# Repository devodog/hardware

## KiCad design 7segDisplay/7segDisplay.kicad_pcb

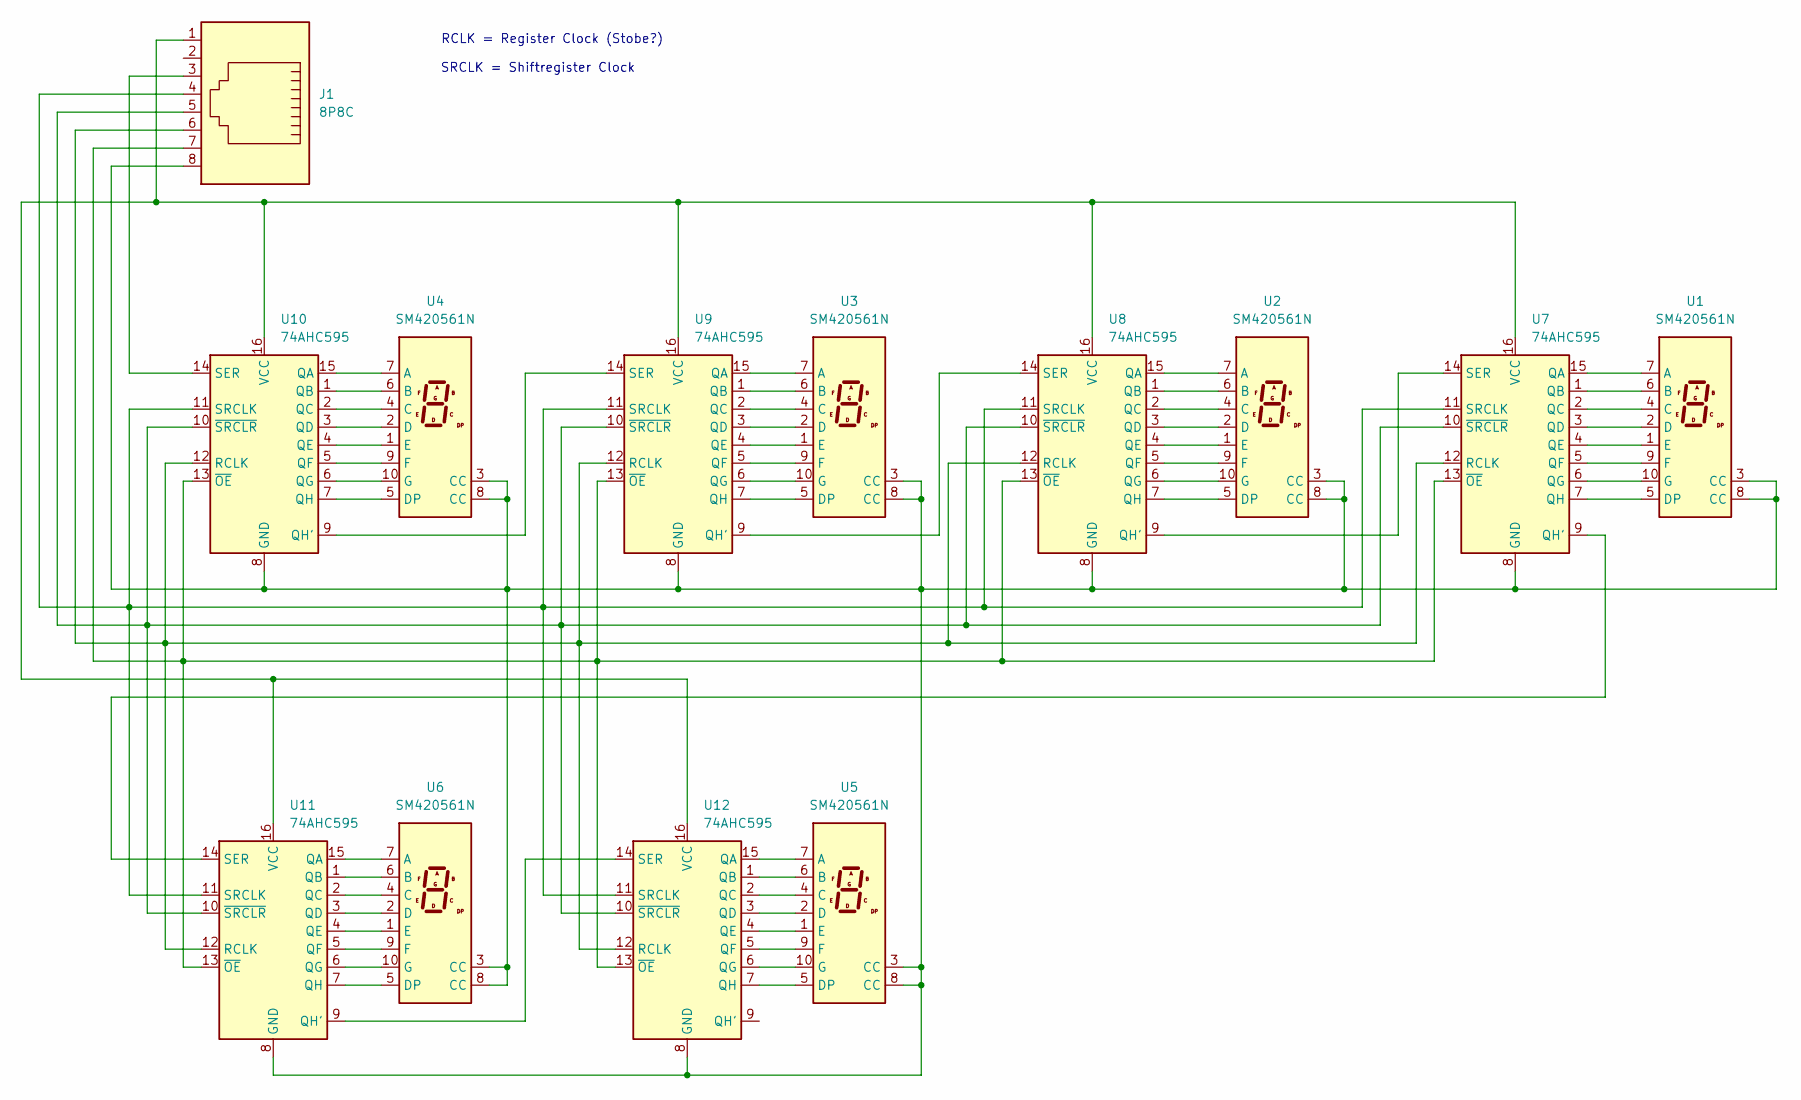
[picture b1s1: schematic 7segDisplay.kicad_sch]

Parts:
J1: 8P8C; RJ45_Amphenol_54602-x08_Horizontal
U1, U2, U3, U4, U5, U6: SM420561N; 7SegmentLED_LTS6760_LTS6780
U7, U8, U9, U10, U11, U12: 74AHC595; DIP-16_W7.62mm_LongPads

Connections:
unnamed: U1.7 (A), U7.15 (QA)
unnamed: U1.6 (B), U7.1 (QB)
unnamed: U1.4 (C), U7.2 (QC)
unnamed: U1.2 (D), U7.3 (QD)
unnamed: U1.5 (DP), U7.7 (QH)
unnamed: U1.1 (E), U7.4 (QE)
unnamed: U1.9 (F), U7.5 (QF)
unnamed: U1.10 (G), U7.6 (QG)
unnamed: U2.7 (A), U8.15 (QA)
unnamed: U2.6 (B), U8.1 (QB)
unnamed: U2.4 (C), U8.2 (QC)
unnamed: U2.2 (D), U8.3 (QD)
unnamed: U2.5 (DP), U8.7 (QH)
unnamed: U2.1 (E), U8.4 (QE)
unnamed: U2.9 (F), U8.5 (QF)
unnamed: U2.10 (G), U8.6 (QG)
unnamed: U3.7 (A), U9.15 (QA)
unnamed: U3.6 (B), U9.1 (QB)
unnamed: U3.4 (C), U9.2 (QC)
unnamed: U3.2 (D), U9.3 (QD)
unnamed: U3.5 (DP), U9.7 (QH)
unnamed: U3.1 (E), U9.4 (QE)
unnamed: U3.9 (F), U9.5 (QF)
unnamed: U3.10 (G), U9.6 (QG)
unnamed: U7.14 (SER), U8.9 (QH')
unnamed: U8.14 (SER), U9.9 (QH')
unnamed: J1.8, U1.3 (CC), U1.8 (CC), U2.3 (CC), U2.8 (CC), U3.3 (CC), U3.8 (CC), U4.3 (CC), U4.8 (CC), U5.3 (CC), U5.8 (CC), U6.3 (CC), U6.8 (CC), U7.8 (GND), U8.8 (GND), U9.8 (GND), U10.8 (GND), U11.8 (GND), U12.8 (GND)
unnamed: U4.7 (A), U10.15 (QA)
unnamed: U4.6 (B), U10.1 (QB)
unnamed: U4.4 (C), U10.2 (QC)
unnamed: U4.2 (D), U10.3 (QD)
unnamed: U4.1 (E), U10.4 (QE)
unnamed: U4.9 (F), U10.5 (QF)
unnamed: U4.10 (G), U10.6 (QG)
unnamed: U9.14 (SER), U10.9 (QH')
unnamed: U4.5 (DP), U10.7 (QH)
unnamed: J1.6, U7.12 (RCLK), U8.12 (RCLK), U9.12 (RCLK), U10.12 (RCLK), U11.12 (RCLK), U12.12 (RCLK)
unnamed: J1.3, U10.14 (SER)
unnamed: J1.4, U7.11 (SRCLK), U8.11 (SRCLK), U9.11 (SRCLK), U10.11 (SRCLK), U11.11 (SRCLK), U12.11 (SRCLK)
unnamed: J1.1, U7.16 (VCC), U8.16 (VCC), U9.16 (VCC), U10.16 (VCC), U11.16 (VCC), U12.16 (VCC)
unnamed: J1.7, U7.13 (~OE), U8.13 (~OE), U9.13 (~OE), U10.13 (~OE), U11.13 (~OE), U12.13 (~OE)
unnamed: J1.5, U7.10 (~SRCLR), U8.10 (~SRCLR), U9.10 (~SRCLR), U10.10 (~SRCLR), U11.10 (~SRCLR), U12.10 (~SRCLR)
unnamed: U6.7 (A), U11.15 (QA)
unnamed: U6.6 (B), U11.1 (QB)
unnamed: U6.4 (C), U11.2 (QC)
unnamed: U6.2 (D), U11.3 (QD)
unnamed: U6.1 (E), U11.4 (QE)
unnamed: U6.9 (F), U11.5 (QF)
unnamed: U6.10 (G), U11.6 (QG)
unnamed: U11.9 (QH'), U12.14 (SER)
unnamed: U6.5 (DP), U11.7 (QH)
unnamed: U7.9 (QH'), U11.14 (SER)
unnamed: U5.7 (A), U12.15 (QA)
unnamed: U5.6 (B), U12.1 (QB)
unnamed: U5.4 (C), U12.2 (QC)
unnamed: U5.2 (D), U12.3 (QD)
unnamed: U5.1 (E), U12.4 (QE)
unnamed: U5.9 (F), U12.5 (QF)
unnamed: U5.10 (G), U12.6 (QG)
unnamed: U5.5 (DP), U12.7 (QH)

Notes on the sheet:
SRCLK = Shiftregister Clock
RCLK = Register Clock (Stobe?)

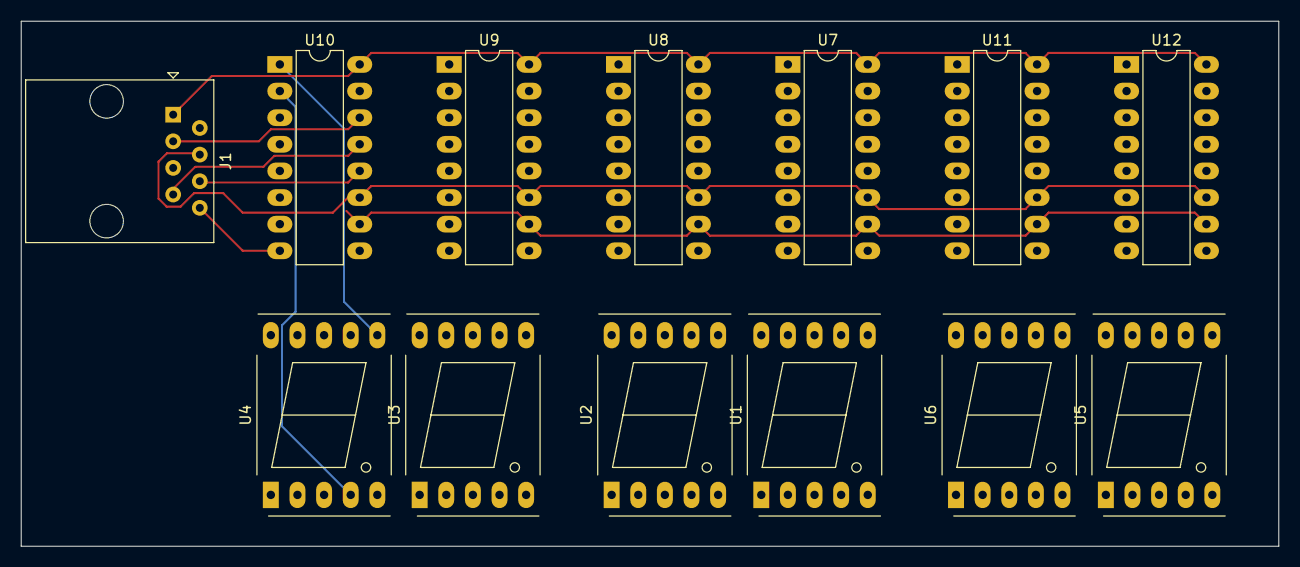
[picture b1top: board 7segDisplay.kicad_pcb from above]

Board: 2 copper layers, 120.0 x 50.1 mm, 13 parts (0 on the bottom side), 60 nets.

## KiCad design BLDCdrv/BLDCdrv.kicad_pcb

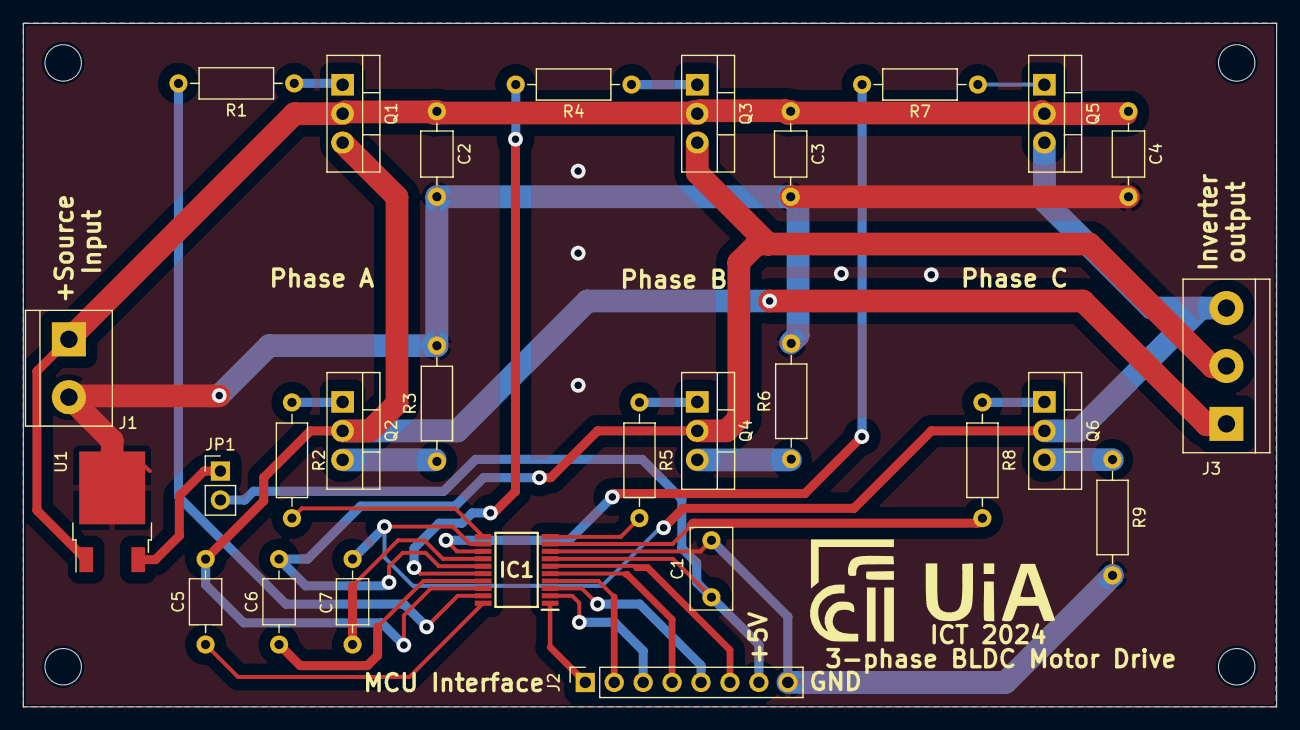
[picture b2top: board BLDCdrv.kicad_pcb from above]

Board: 2 copper layers, 110.0 x 60.0 mm, 28 parts (0 on the bottom side), 31 nets.

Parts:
C1: 1000n; C_Rect_L7.0mm_W3.5mm_P5.00mm
C2, C3, C4, C5, C6, C7: 100n; C_Axial_L3.8mm_D2.6mm_P7.50mm_Horizontal
IC1: DRV8300DIPWR; SOP65P640X120-20N
J1: Screw_Terminal_01x02; TerminalBlock_bornier-2_P5.08mm
J2: Conn_01x08_Male; PinSocket_1x08_P2.54mm_Vertical
J3: Screw_Terminal_01x03; TerminalBlock_bornier-3_P5.08mm
JP1: Jumper_2_Open; PinHeader_1x02_P2.54mm_Vertical
Q1, Q2, Q3, Q4, Q5, Q6: IRF540N; TO-220-3_Vertical
R1, R2, R4, R5, R7, R8: 15; R_Axial_DIN0207_L6.3mm_D2.5mm_P10.16mm_Horizontal
R3, R6, R9: 0; R_Axial_DIN0207_L6.3mm_D2.5mm_P10.16mm_Horizontal
U1: LF50_TO252; TO-252-2

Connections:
+BATT: C2.1, C3.1, C4.1, J1.1, Q1.2 (D), Q3.2 (D), Q5.2 (D), U1.1 (VI)
GNDREF: C1.2, C2.2, C3.2, C4.2, IC1.8 (GND), J1.2, J2.8, R3.2, R6.2, R9.2, U1.2 (GND)
unnamed: C1.1, IC1.7 (GVDD), J2.7, JP1.2 (B)
unnamed: C5.1, IC1.20 (BSTA)
unnamed: C5.2, IC1.18 (SHA), J3.1, Q1.3 (S), Q2.2 (D)
unnamed: C6.1, IC1.17 (BSTB)
unnamed: C6.2, IC1.15 (SHB), J3.2, Q3.3 (S), Q4.2 (D)
unnamed: C7.1, IC1.14 (BSTC)
unnamed: C7.2, IC1.12 (SHC), J3.3, Q5.3 (S), Q6.2 (D)
unnamed: IC1.1 (INHA), J2.1
unnamed: IC1.2 (INHB), J2.3
unnamed: IC1.3 (INHC), J2.5
unnamed: IC1.4 (INLA), J2.2
unnamed: IC1.5 (INLB), J2.4
unnamed: IC1.6 (INLC), J2.6
unnamed: IC1.9 (GLC), R8.2
unnamed: IC1.10 (GLB), R5.2
unnamed: IC1.11 (GLA), R2.2
unnamed: IC1.13 (GHC), R7.2
unnamed: IC1.16 (GHB), R4.2
unnamed: IC1.19 (GHA), R1.2
unnamed: JP1.1 (A), U1.3 (VO)
unnamed: Q1.1 (G), R1.1
unnamed: Q2.1 (G), R2.1
unnamed: Q2.3 (S), R3.1
unnamed: Q3.1 (G), R4.1
unnamed: Q4.1 (G), R5.1
unnamed: Q4.3 (S), R6.1
unnamed: Q5.1 (G), R7.1
unnamed: Q6.1 (G), R8.1
unnamed: Q6.3 (S), R9.1

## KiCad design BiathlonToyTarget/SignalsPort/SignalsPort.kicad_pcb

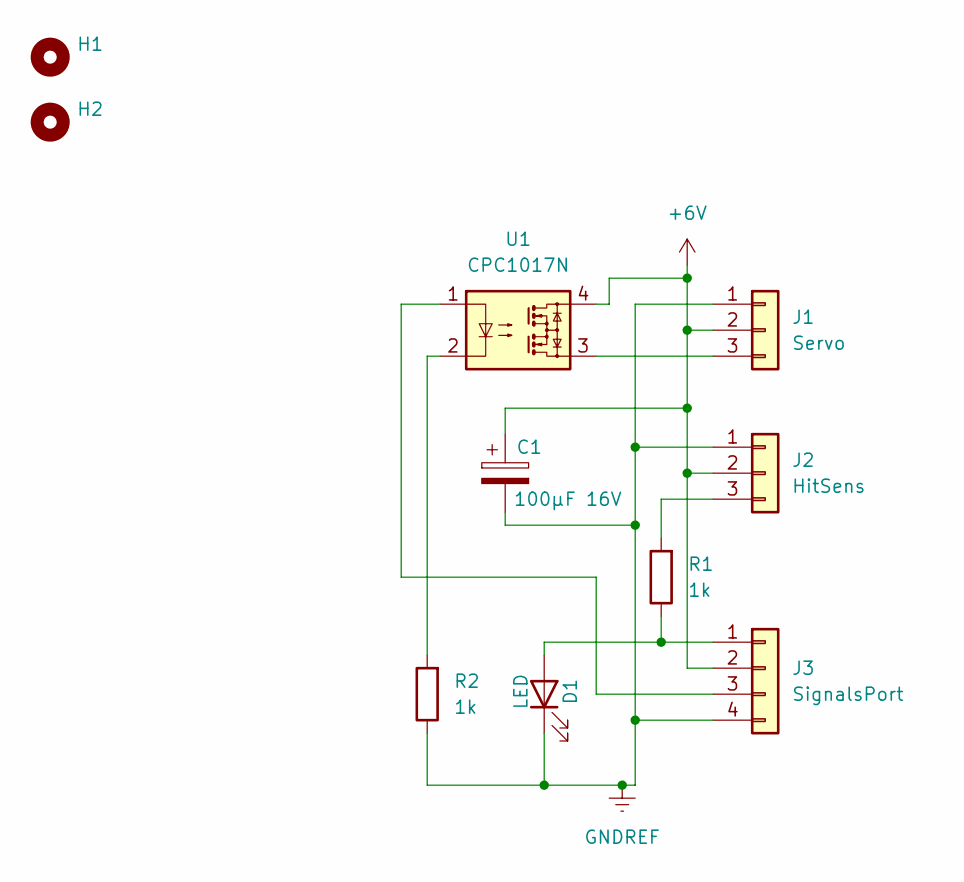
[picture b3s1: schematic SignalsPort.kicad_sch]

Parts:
C1: 100µF 16V; C_Elec_6.3x7.7
D1: LED; LED_0805_2012Metric_Pad1.15x1.40mm_HandSolder
H1, H2: MountingHole; MountingHole_3.2mm_M3
J1: Servo; PinHeader_1x03_P2.54mm_Horizontal
J2: HitSens; PinHeader_1x03_P2.54mm_Horizontal
J3: SignalsPort; Hirose_DF3EA-04P-2H_1x04-1MP_P2.00mm_Horizontal
R1, R2: 1k; R_0805_2012Metric_Pad1.20x1.40mm_HandSolder
U1: CPC1017N; SOP-4_3.8x4.1mm_P2.54mm

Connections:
+6V: C1.1, J1.2, J2.2, J3.2, U1.4
GNDREF: C1.2, D1.1 (K), J1.1, J2.1, J3.4, R2.1
unnamed: D1.2 (A), J3.1, R1.1
unnamed: J1.3, U1.3
unnamed: J2.3, R1.2
unnamed: J3.3, U1.1
unnamed: R2.2, U1.2

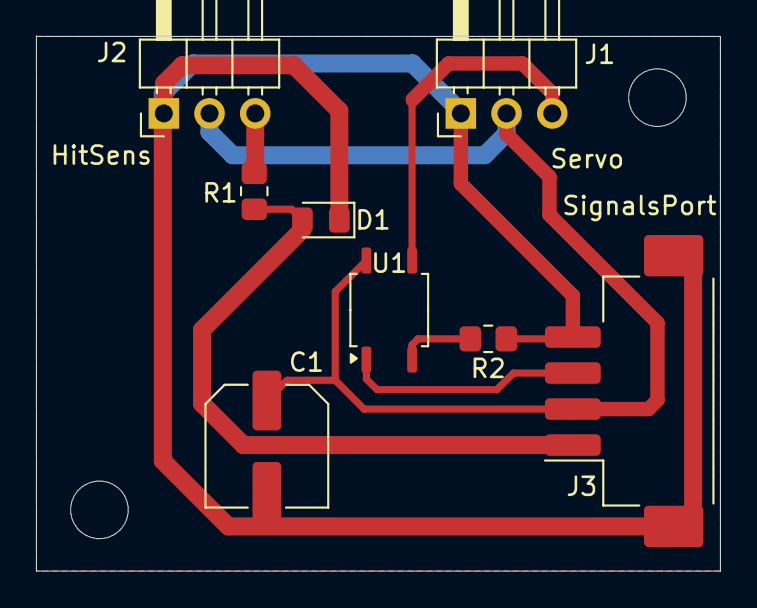
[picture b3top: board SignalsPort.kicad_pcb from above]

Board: 2 copper layers, 38.0 x 29.7 mm, 10 parts (0 on the bottom side), 7 nets.

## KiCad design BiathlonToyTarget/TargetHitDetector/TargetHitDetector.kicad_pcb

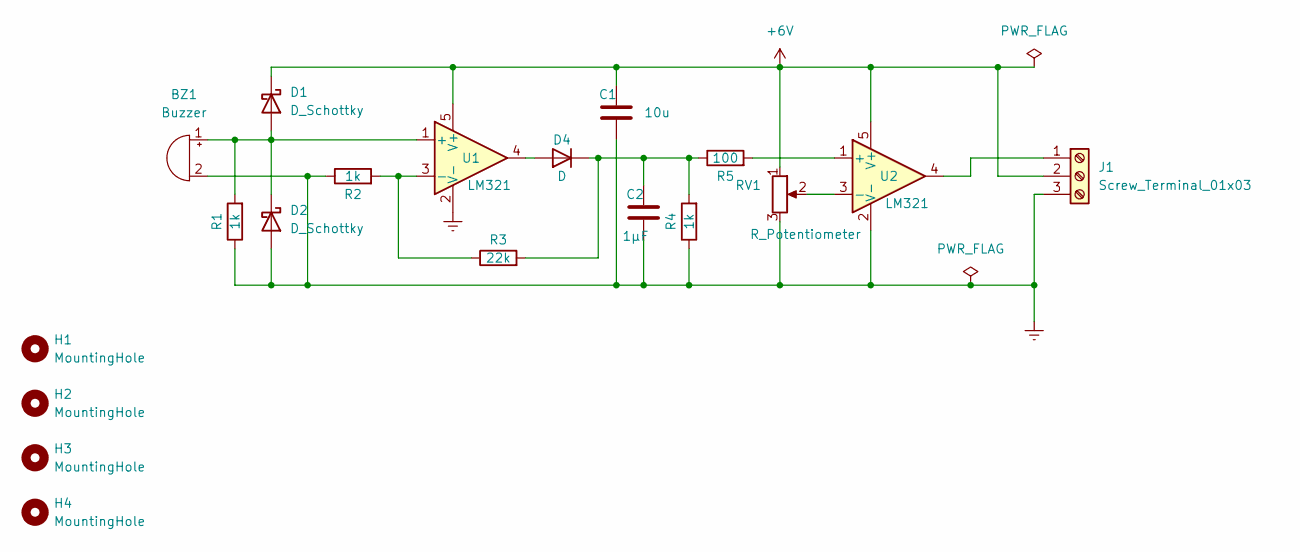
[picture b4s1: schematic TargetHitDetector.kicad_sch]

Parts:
BZ1: Buzzer; Buzzer_Murata_PKMCS0909E
C1: 10u; C_1206_3216Metric_Pad1.33x1.80mm_HandSolder
C2: 1µF; C_1206_3216Metric_Pad1.33x1.80mm_HandSolder
D1, D2: D_Schottky; D_SOD-523
D4: D; D_1206_3216Metric_Pad1.42x1.75mm_HandSolder
H1, H2, H3, H4: MountingHole; MountingHole_3.2mm_M3
J1: Screw_Terminal_01x03; Wago_734-133_1x03_P3.50mm_Vertical
R1, R2, R4: 1k; R_1206_3216Metric_Pad1.30x1.75mm_HandSolder
R3: 22k; R_1206_3216Metric_Pad1.30x1.75mm_HandSolder
R5: 100; R_1206_3216Metric_Pad1.30x1.75mm_HandSolder
RV1: R_Potentiometer; Potentiometer_ACP_CA9-H5_Horizontal
U1, U2: LM321; SOT-23-5

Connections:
+6V: C1.1, D1.1 (K), J1.2, RV1.1, U1.5 (V+), U2.5 (V+)
Earth: BZ1.2 (+), C1.2, C2.2, D2.2 (A), J1.3, R1.1, R2.1, R4.1, RV1.3, U1.2 (V-), U2.2 (V-)
unnamed: BZ1.1 (-), D1.2 (A), D2.1 (K), R1.2, U1.1 (+)
unnamed: D4.2 (A), U1.4
unnamed: C2.1, D4.1 (K), R3.2, R4.2, R5.1
unnamed: J1.1, U2.4
unnamed: R2.2, R3.1, U1.3 (-)
unnamed: R5.2, U2.1 (+)
unnamed: RV1.2, U2.3 (-)

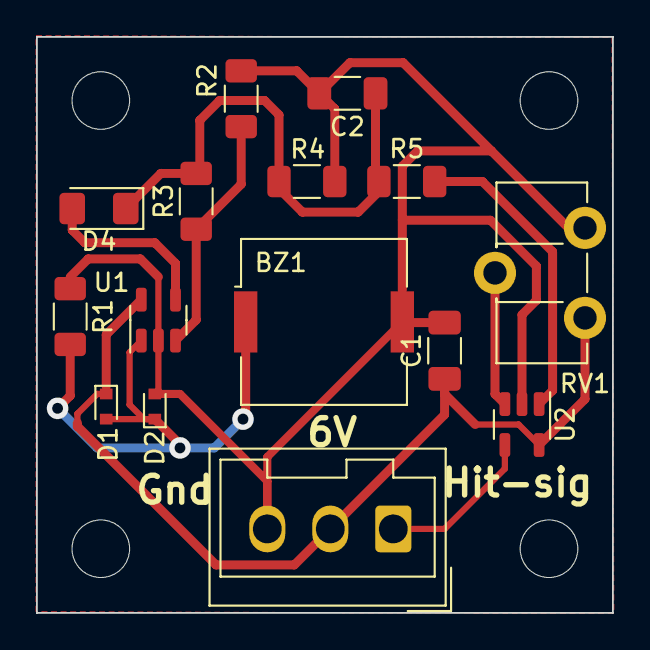
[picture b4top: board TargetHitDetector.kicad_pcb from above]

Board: 2 copper layers, 32.0 x 32.0 mm, 19 parts (0 on the bottom side), 9 nets.

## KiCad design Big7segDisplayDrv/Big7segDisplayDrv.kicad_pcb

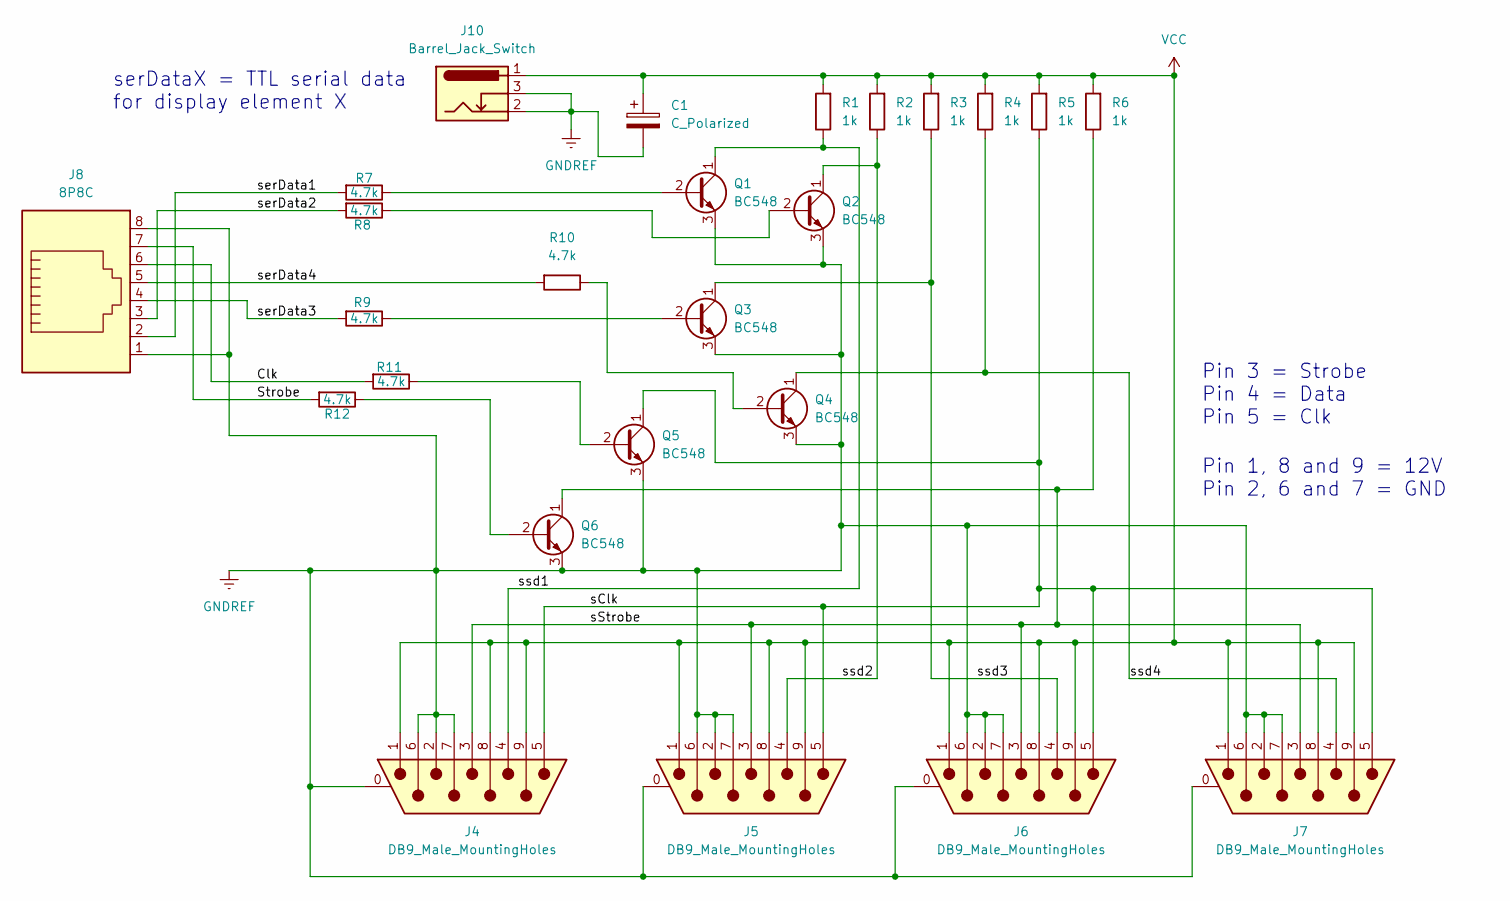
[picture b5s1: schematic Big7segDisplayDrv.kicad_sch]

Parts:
C1: C_Polarized; CP_Radial_D10.0mm_P5.00mm
J4, J5, J6, J7: DB9_Male_MountingHoles; DSUB-9_Male_Horizontal_P2.77x2.84mm_EdgePinOffset9.90mm_Hou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
J8: 8P8C; RJ45_Amphenol_54602-x08_Horizontal
J10: Barrel_Jack_Switch; BarrelJack_GCT_DCJ200-10-A_Horizontal
Q1, Q2, Q3, Q4, Q5, Q6: BC548; TO-92_HandSolder
R1, R2, R3, R4, R5, R6: 1k; R_Axial_DIN0207_L6.3mm_D2.5mm_P10.16mm_Horizontal
R7, R8, R9, R10, R11, R12: 4.7k; R_Axial_DIN0207_L6.3mm_D2.5mm_P10.16mm_Horizontal

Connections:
/Clk: J8.6, R11.2
/Strobe: J8.7, R12.2
/sClk: J4.5, J5.5, J6.5, J7.5, Q5.1 (C), R5.1
/sStrobe: J4.3, J5.3, J6.3, J7.3, Q6.1 (C), R6.1
/serData1: J8.2, R7.2
/serData2: J8.3, R8.2
/serData3: J8.4, R9.2
/serData4: J8.5, R10.2
/ssd1: J4.4, Q1.1 (C), R1.1
/ssd2: J5.4, Q2.1 (C), R2.1
/ssd3: J6.4, Q3.1 (C), R3.1
/ssd4: J7.4, Q4.1 (C), R4.1
GNDREF: C1.2, J4.0 (PAD), J4.2, J4.6, J4.7, J5.0 (PAD), J5.2, J5.6, J5.7, J6.0 (PAD), J6.2, J6.6, J6.7, J7.0 (PAD), J7.2, J7.6, J7.7, J8.1, J8.8, J10.2, J10.3, Q1.3 (E), Q2.3 (E), Q3.3 (E), Q4.3 (E), Q5.3 (E), Q6.3 (E)
unnamed: Q1.2 (B), R7.1
unnamed: Q2.2 (B), R8.1
unnamed: Q3.2 (B), R9.1
unnamed: Q4.2 (B), R10.1
unnamed: Q5.2 (B), R11.1
unnamed: Q6.2 (B), R12.1
VCC: C1.1, J4.1, J4.8, J4.9, J5.1, J5.8, J5.9, J6.1, J6.8, J6.9, J7.1, J7.8, J7.9, J10.1, R1.2, R2.2, R3.2, R4.2, R5.2, R6.2

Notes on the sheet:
Pin 1, 8 and 9 = 12V Pin 2, 6 and 7 = GND
Pin 3 = Strobe Pin 4 = Data Pin 5 = Clk
serDataX = TTL serial data for display element X

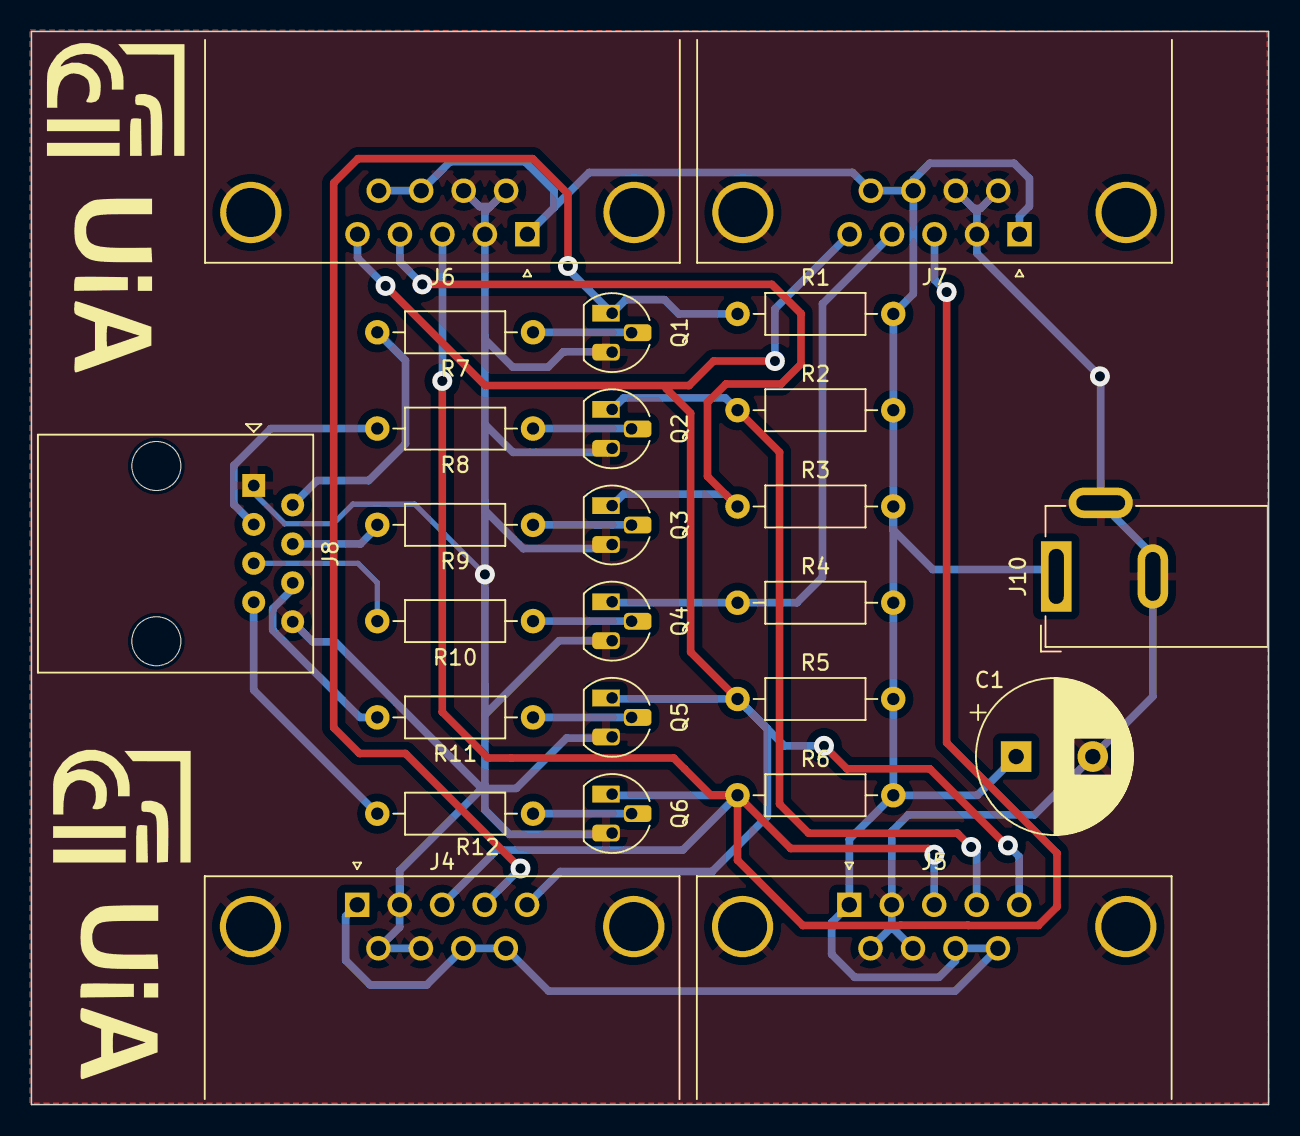
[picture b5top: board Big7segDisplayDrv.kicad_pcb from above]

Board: 2 copper layers, 80.7 x 70.0 mm, 25 parts (0 on the bottom side), 20 nets.

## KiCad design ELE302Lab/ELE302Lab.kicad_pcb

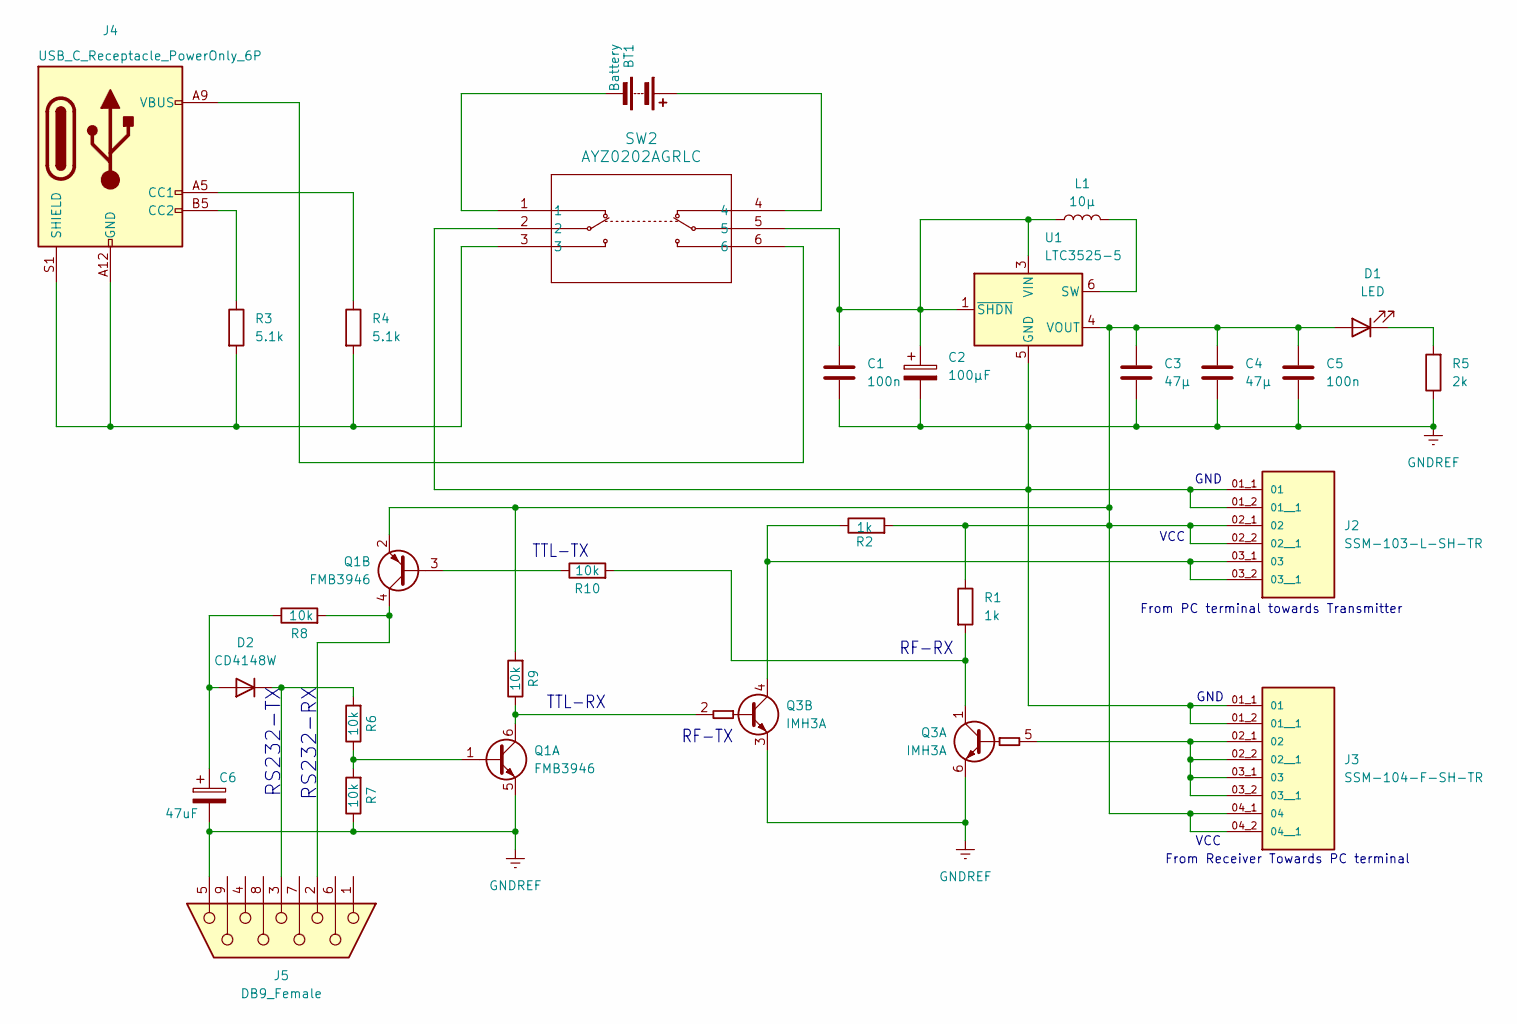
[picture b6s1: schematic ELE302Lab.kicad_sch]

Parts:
BT1: Battery; BatteryHolder_Keystone_2479_3xAAA
C1, C5: 100n; C_0805_2012Metric_Pad1.18x1.45mm_HandSolder
C2: 100µF; CP_Elec_6.3x9.9
C3, C4: 47µ; C_1206_3216Metric_Pad1.33x1.80mm_HandSolder
C6: 47uF; C_1206_3216Metric_Pad1.33x1.80mm_HandSolder
D1: LED; LED_1206_3216Metric
D2: CD4148W; D_0805_2012Metric
J2: SSM-103-L-SH-TR; SAMTEC_SSM-103-L-SH-TR
J3: SSM-104-F-SH-TR; SAMTEC_SSM-104-F-SH-TR
J4: USB_C_Receptacle_PowerOnly_6P; USB_C_Receptacle_GCT_USB4135-GF-A_6P_TopMnt_Horizontal
J5: DB9_Female; DSUB-9_Female_Horizontal_P2.77x2.84mm_EdgePinOffset9.90mm_H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
L1: 10µ; IND_ELLVFG_PAN
Q1: FMB3946; TSOT-23-6_HandSoldering
Q3: IMH3A; ROHM_SOT-457_ClockwisePinNumbering
R1, R2: 1k; R_1206_3216Metric_Pad1.30x1.75mm_HandSolder
R3, R4: 5.1k; R_1206_3216Metric_Pad1.30x1.75mm_HandSolder
R5: 2k; R_1206_3216Metric_Pad1.30x1.75mm_HandSolder
R6, R7, R8, R9, R10: 10k; R_1206_3216Metric_Pad1.30x1.75mm_HandSolder
SW2: AYZ0202AGRLC; AYZ0202AGRLC_CNK
U1: LTC3525-5; SOT-363_SC-70-6

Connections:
GNDREF: C1.2, C2.2, C3.2, C4.2, C5.2, C6.2, J2.01_1 (01), J2.01_2 (01__1), J3.01_1 (01), J3.01_2 (01__1), J5.5, Q1.5 (E1), Q3.3 (E2), Q3.6 (E1), R5.1, R7.1, SW2.2, U1.2 (GND), U1.5 (GND)
unnamed: BT1.1 (+), SW2.4
unnamed: BT1.2 (-), SW2.1
unnamed: C3.1, C4.1, C5.1, D1.2 (A), J2.02_1 (02), J2.02_2 (02__1), J3.04_1 (04), J3.04_2 (04__1), Q1.2 (E2), R1.1, R2.2, R9.2, U1.4 (VOUT)
unnamed: D1.1 (K), R5.2
unnamed: C6.1, D2.2 (A), R8.1
unnamed: D2.1 (K), J5.3, R6.2
unnamed: J2.03_1 (03), J2.03_2 (03__1), Q3.4 (C2), R2.1
unnamed: J3.02_1 (02), J3.02_2 (02__1), J3.03_1 (03), J3.03_2 (03__1), Q3.5 (B1)
unnamed: J4.A5 (CC1), R4.1
unnamed: J4.B5 (CC2), R3.1
unnamed: J4.A12 (GND), J4.B12 (GND), J4.S1 (SHIELD), R3.2, R4.2, SW2.3
unnamed: J4.A9 (VBUS), J4.B9 (VBUS), SW2.6
unnamed: Q1.1 (B1), R6.1, R7.2
unnamed: Q1.6 (C1), Q3.2 (B2), R9.1
unnamed: Q1.3 (B2), R10.1
unnamed: J5.2, Q1.4 (C2), R8.2
unnamed: Q3.1 (C1), R1.2, R10.2
unnamed: L1.2, U1.6 (SW)
unnamed: C1.1, C2.1, L1.1, SW2.5, U1.1 (~SHDN), U1.3 (VIN)

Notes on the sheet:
TTL-RX
VCC
RS232-RX
From PC terminal towards Transmitter
RF-TX
TTL-TX
RF-RX
GND
RS232-TX
From Receiver Towards PC terminal

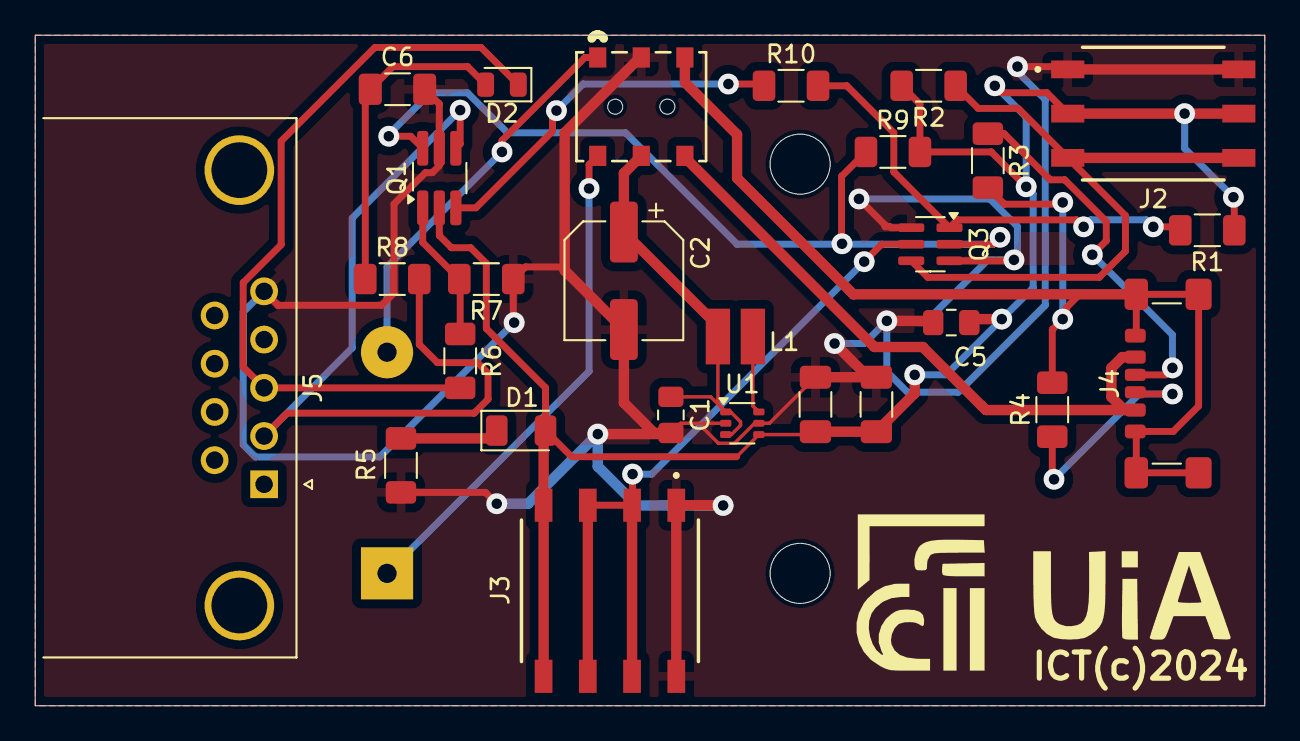
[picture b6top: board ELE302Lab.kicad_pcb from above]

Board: 2 copper layers, 70.6 x 38.5 mm, 28 parts (1 on the bottom side), 20 nets.

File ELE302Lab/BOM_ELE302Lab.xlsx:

Id | Designator | Footprint | Quantity | Designation | quantity | unit price (NOK) | total | Supplier and ref
1 | R2,R3 | R_1206_3216Metric_Pad1.30x1.75mm_HandSolder | 2 | 1k |  |  |  | inhouse
2 | C3,C4 | C_1206_3216Metric_Pad1.33x1.80mm_HandSolder | 2 | 47µF |  |  |  | inhouse
3 | D1 | LED_1206_3216Metric | 1 | LED |  |  |  | inhouse
4 | R4,R1 | R_1206_3216Metric_Pad1.30x1.75mm_HandSolder | 2 | 5.1k |  |  |  | inhouse
5 | L1 | IND_ELLVFG_PAN | 1 | 10µF |  |  |  | inhouse
6 | C2 | CP_Elec_6.3x9.9 | 1 | 100µF |  |  |  | inhouse
7 | C1,C5 | C_0805_2012Metric_Pad1.18x1.45mm_HandSolder | 2 | 100n |  |  |  | inhouse
8 | J2 | SAMTEC_SSM-103-L-SH-TR | 1 | SSM-103-L-SH-TR |  | 19.600000000000001 |  | https://www.digikey.no/en/products/detail/samtec-inc/SSM-103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
9 | SW2 | AYZ0202AGRLC_CNK | 1 | AYZ0202AGRLC |  | 21.47 |  | https://www.digikey.no/en/products/detail/c-k/AYZ0202AGRLC/1640109
10 | U1 | SOT-363_SC-70-6 | 1 | LTC3525-5 |  | 77.95 |  | https://www.digikey.no/en/products/detail/analog-devices-inc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
11 | J4 | USB_C_Receptacle_GCT_USB4135-GF-A_6P_TopMnt_Horizontal | 1 | USB_C_Receptacle_PowerOnly_6P |  | 8.3699999999999992 |  | https://www.digikey.no/en/products/detail/gct/USB4135-GF-A/16036137
12 | J3,J1 | SAMTEC_SSM-104-F-SH-TR | 2 | SSM-104-F-SH-TR |  | 18.61 |  | https://www.digikey.no/en/products/detail/samtec-inc/ssm-104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
13 | Q3 | ROHM_SOT-457_ClockwisePinNumbering | 1 | IMH3A |  | 4.1900000000000004 |  | https://no.mouser.com/ProductDetail/ROHM-Semiconductor/IMH4A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
14 | R5 | R_1206_3216Metric_Pad1.30x1.75mm_HandSolder | 1 | 2k |  |  |  | inhouse
15 | BT1 | BatteryHolder_Keystone_2479_3xAAA | 1 | Battery |  |  |  | inhouse
 |  |  |  |  |  | 150.19

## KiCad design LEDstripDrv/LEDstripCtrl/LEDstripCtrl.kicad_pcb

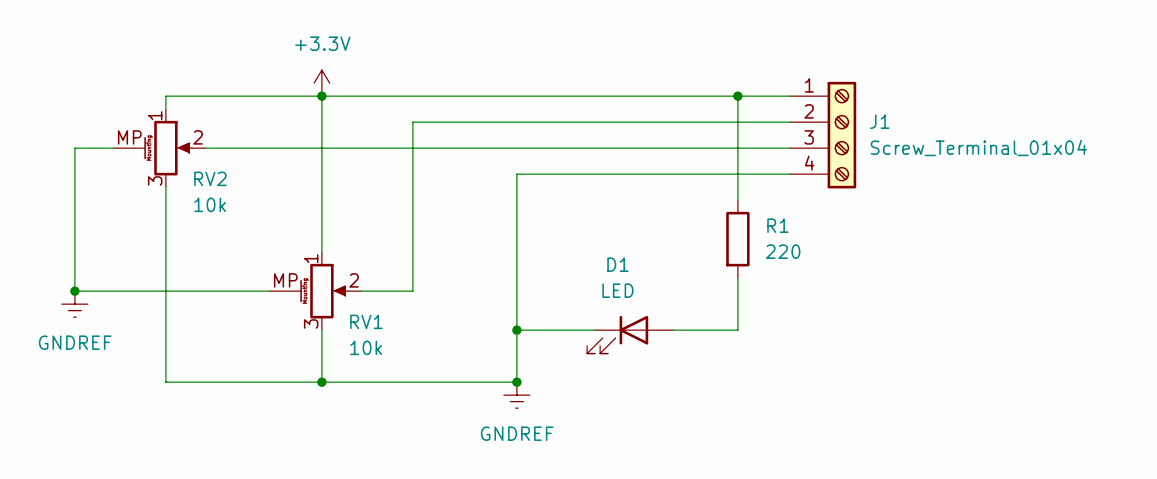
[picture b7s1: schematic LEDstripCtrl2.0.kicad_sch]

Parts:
D1: LED; LED_D3.0mm
J1: Screw_Terminal_01x04; TerminalBlock_Phoenix_MKDS-1,5-4-5.08_1x04_P5.08mm_Horizont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
R1: 220; R_Axial_DIN0309_L9.0mm_D3.2mm_P12.70mm_Horizontal
RV1, RV2: 10k; Potentiometer_Bourns_PTA4543_Single_Slide

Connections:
+3.3V: J1.1, R1.1, RV1.1, RV2.1
GNDREF: D1.1 (K), J1.4, RV1.3, RV1.MP (MountPin), RV2.3, RV2.MP (MountPin)
unnamed: D1.2 (A), R1.2
unnamed: J1.2, RV1.2
unnamed: J1.3, RV2.2

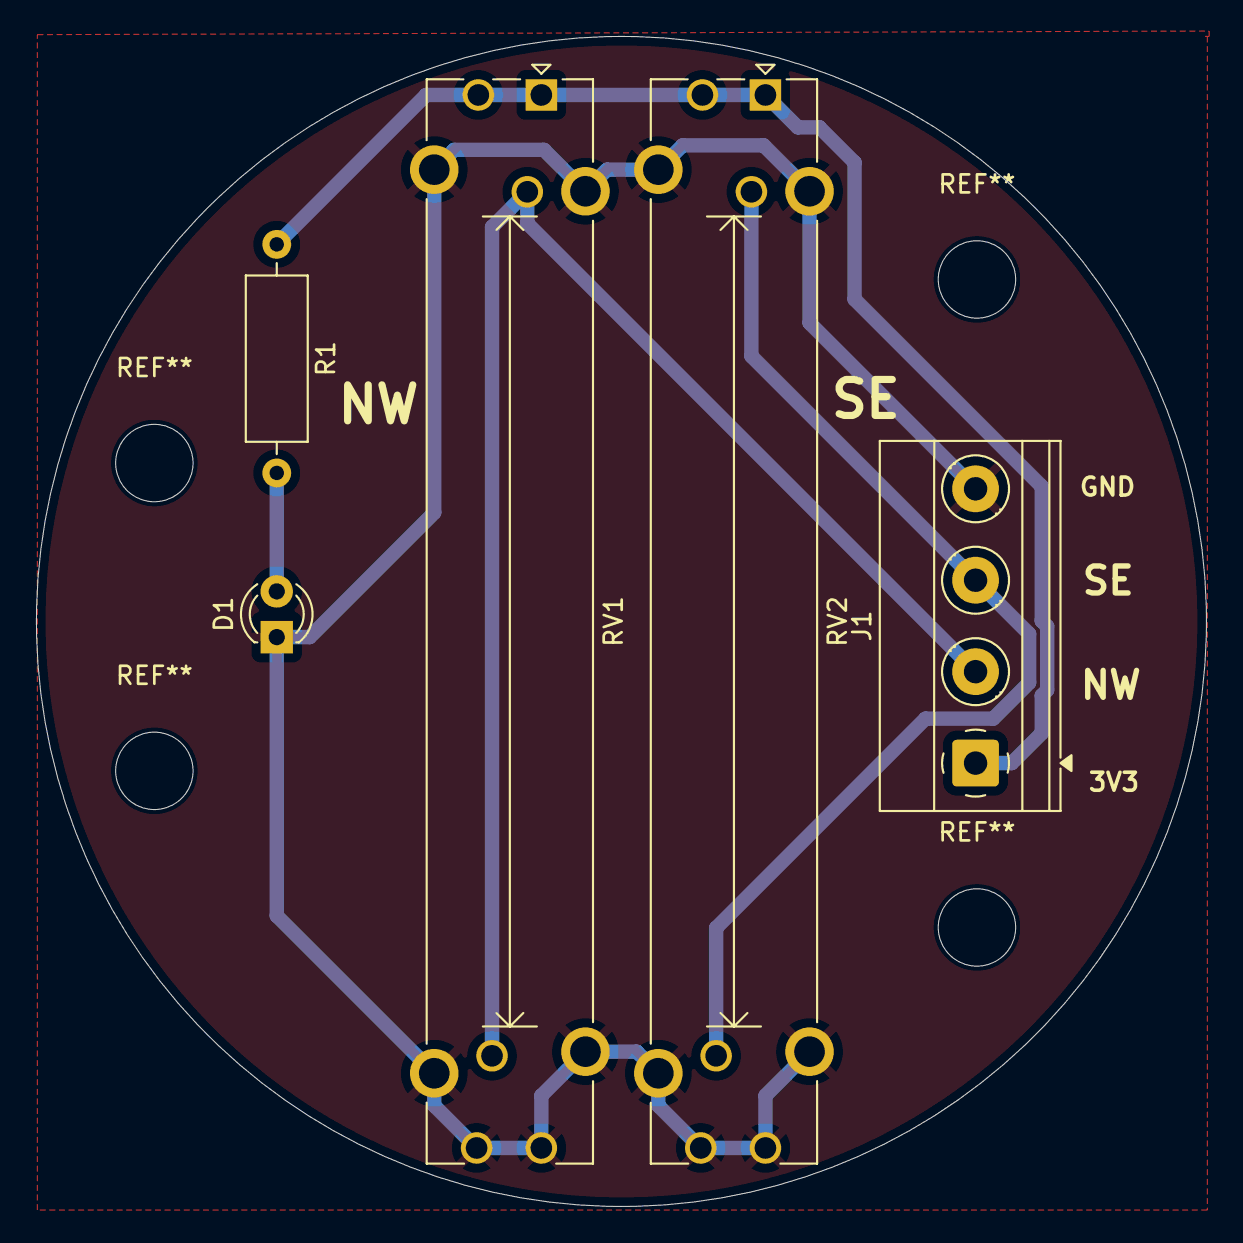
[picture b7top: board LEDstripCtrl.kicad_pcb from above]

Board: 2 copper layers, 65.0 x 65.0 mm, 5 parts (0 on the bottom side), 5 nets.

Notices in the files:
ELE302Lab/ELE302Lab.kicad_pcb:
ICT(c)2024
